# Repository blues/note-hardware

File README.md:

# note-hardware

This repository contains open hardware designs for Notecarriers and other Notecard-related hardware available through our [online store](https://shop.blues.com).

## Designs

|Item|Description|Contents|
|---|---|---|
|[Notecard](Notecard)|Device-to-cloud data pump|Dimensioned drawings and 3D models|
|[Notecarrier A](Notecarrier-A)|Carrier for battery- and solar-powered wireless applications|Full electrical and mechanical design, plus KiCad|
|[Notecarrier CX](Notecarrier-CX)|Carrier with an onboard STM32L433 MCU|Full electrical and mechanical design, plus KiCad|
|[Notecarrier F](Notecarrier-F)|Carrier for Adafruit Feather-compatible hosts|Full electrical and mechanical design, plus KiCad|
|[Notecarrier Pi](Notecarrier-Pi)|Carrier with a Raspberry Pi-compatible hardware interface|Full electrical and mechanical design, plus KiCad|
|[Notecarrier X](Notecarrier-X)|Small form-factor carrier with Qwiic and ESLOV ports|Full electrical and mechanical design, plus KiCad|
|[Notecarrier XI](Notecarrier-XI)|Companion carrier for Starnote for Iridium|Full electrical and mechanical design, plus KiCad|
|[Notecarrier XM](Notecarrier-XM)|Minimal small form-factor carrier, without an external SIM slot|Full electrical and mechanical design, plus KiCad|
|[Notecarrier XP](Notecarrier-XP)|Companion carrier for the Notecard XP|Full electrical and mechanical design|
|[Notecarrier XS](Notecarrier-XS)|Ultra-compact small form-factor carrier|Full electrical and mechanical design, plus KiCad|
|[Cygnet](Cygnet)|STM32L433 in Adafruit Feather form factor|Full electrical design, plus KiCad|
|[Swan](Swan)|STM32L4R5 in Adafruit Feather form factor|Full electrical and mechanical design|
|[Starnote](Starnote)|Satellite Notecard companion|3D models|
|[Scoop](Scoop)|Supercapacitor backup power for Notecard applications|Full electrical and mechanical design, plus KiCad|
|[Mojo](Mojo)|Energy-usage measurement for battery-powered systems|Full electrical and mechanical design, plus KiCad|
|[Airnote](Airnote)|Air quality monitor powered by Notecard|Enclosure 3D models and drawings|
|[Wireless for OPTA](Wireless%20for%20OPTA)|Cellular and Wi-Fi connectivity for Arduino Opta|3D model|
|[3D Models for Enclosures](3D%20Models%20for%20Enclosures)|Community-contributed enclosures, not supported by Blues|Printable STL and STEP models|
|[_Legacy Hardware](_Legacy%20Hardware)|Components and designs no longer sold|Assorted design files|

Each directory has its own README describing the available versions, the design
file formats, and any caveats that apply to that board.

## More Information

Various other resources that may be useful as you develop hardware around Notecard and Notecarriers.

### Application Notes

* [Antenna Guide](https://dev.blues.io/datasheets/application-notes/antenna-guide/)
* [Blues Security, Reliability, and Governance](https://dev.blues.io/datasheets/application-notes/blues-security-reliability-and-governance/)
* [Designing for XP Variants of the Blues Notecard](https://dev.blues.io/datasheets/application-notes/designing-for-xp-variants-of-the-blues-notecard/)
* [Low-Power Hardware Design](https://dev.blues.io/datasheets/application-notes/low-power-hardware-design/)
* [Notecard Carrier Board Design Guide](https://dev.blues.io/datasheets/application-notes/notecard-carrier-board-design-guide/)
* [Notecard Real-Time Clock](https://dev.blues.io/datasheets/application-notes/notecard-real-time-clock/)
* [Notecarrier A Series Solar JST Input](https://dev.blues.io/datasheets/application-notes/notecarrier-a-series-solar-jst-input/)
* [Starnote Carrier Board Design Guide](https://dev.blues.io/datasheets/application-notes/starnote-carrier-board-design-guide/)

### Tooling

The [_Tools](_Tools) directory holds the utilities used to maintain this
repository, including the KiCad validation harness that checks the KiCad ports
against the shipped fabrication packages.

### Learn more about Blues, Notecard, and Notehub

* [blues.com](https://blues.com)
* [notehub.io](https://notehub.io)
* [dev.blues.io](https://dev.blues.io)

## Contributing

We love issues, fixes, and pull requests from everyone. By participating in this
project, you agree to abide by the Blues Inc.
[code of conduct](CODE_OF_CONDUCT.md).

For details on contributions we accept and the process for contributing, see our
[contribution guide](CONTRIBUTING.md).

## License

Copyright (c) 2026 Blues Inc. Released under the MIT license. See
[LICENSE](LICENSE) for details.

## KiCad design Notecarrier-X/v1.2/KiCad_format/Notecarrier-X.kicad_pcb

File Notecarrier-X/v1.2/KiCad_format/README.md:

# Notecarrier-X — KiCad format

This directory contains the design files for the Blues **Notecarrier-X**
in **KiCad 9** format, ported from the internal Altium Designer sources
(project `100379_notecarrier-x`, Byte Lab Grupa d.o.o. for Blues) and
validated against the shipped production BOM and the published v1.2
fabrication package — see
[`documentation/Porting-Notes.md`](documentation/Porting-Notes.md) and
[`validation/`](validation/).

Generated from the design house's **Rev-11 release snapshot** — the Altium
sources behind the published v1.2 fab package (`2200-918`). Copper, solder mask
and paste match that fab package to within raster resolution, and every pad's
net matches the released board. An earlier version of this port was built from a post-v1.2
development state and carried a source-fidelity disclaimer; it was
regenerated from Rev-11 in October 2026 and the disclaimer retired (see the
Porting-Notes history section).

## Contents

| Path | Description |
|---|---|
| `Notecarrier-X.kicad_pro` / `.kicad_prl` | KiCad project |
| `Notecarrier-X.kicad_sch` | Root schematic sheet |
| `Notecarrier-X_IO-Connection.kicad_sch` | IO connection sheet |
| `Notecarrier-X_Notecard-Connection.kicad_sch` | Notecard connection sheet |
| `Notecarrier-X_Power.kicad_sch` | Power sheet |
| `Notecarrier-X.kicad_pcb` | 2-layer board (zone fills preserved from the Altium import — do not refill) |
| `Notecarrier-X.kicad_wks` | Drawing sheet (shared Blues template) |
| `Notecarrier-X-altium-import.kicad_sym` / `.pretty/` | Project libraries captured during the import |
| `sym-lib-table` / `fp-lib-table` | Library tables |
| `documentation/` | Porting notes (provenance and verification), plotted PDFs, and the board-regeneration scripts (`scripts/`, also used for Notecarrier-XM) |
| `manufacturing/Notecarrier-X_RevA.zip` | KiCad-exported gerbers + drill |
| `validation/` | Validation-gate artifacts (ERC/DRC/BOM reports, per-layer gerber diffs, kicanvas renders) |

The schematic references the shared Blues symbol/footprint library via the
`BLUES_KICAD_LIB_DIR` path variable
([blues-kicad-lib](https://github.com/blues/blues-kicad-lib)), with all
symbols and footprints used by this design also embedded in the project
libraries above, so the project opens standalone.

## Provenance

Ported from Altium Designer sources with KiCad 9.0.9's importer and the
validation harness in
[`_Tools/kicad_validation/`](../../../_Tools/kicad_validation/). The original
Altium sources are internal and are not part of this repository; the
published v1.2 fabrication package (`../2200-918__2024-06-06.zip`), BOM
(`../BOM-3000-794-001.xlsx`) and drawings in the parent folder remain the
manufacturing ground truth for the shipped product.

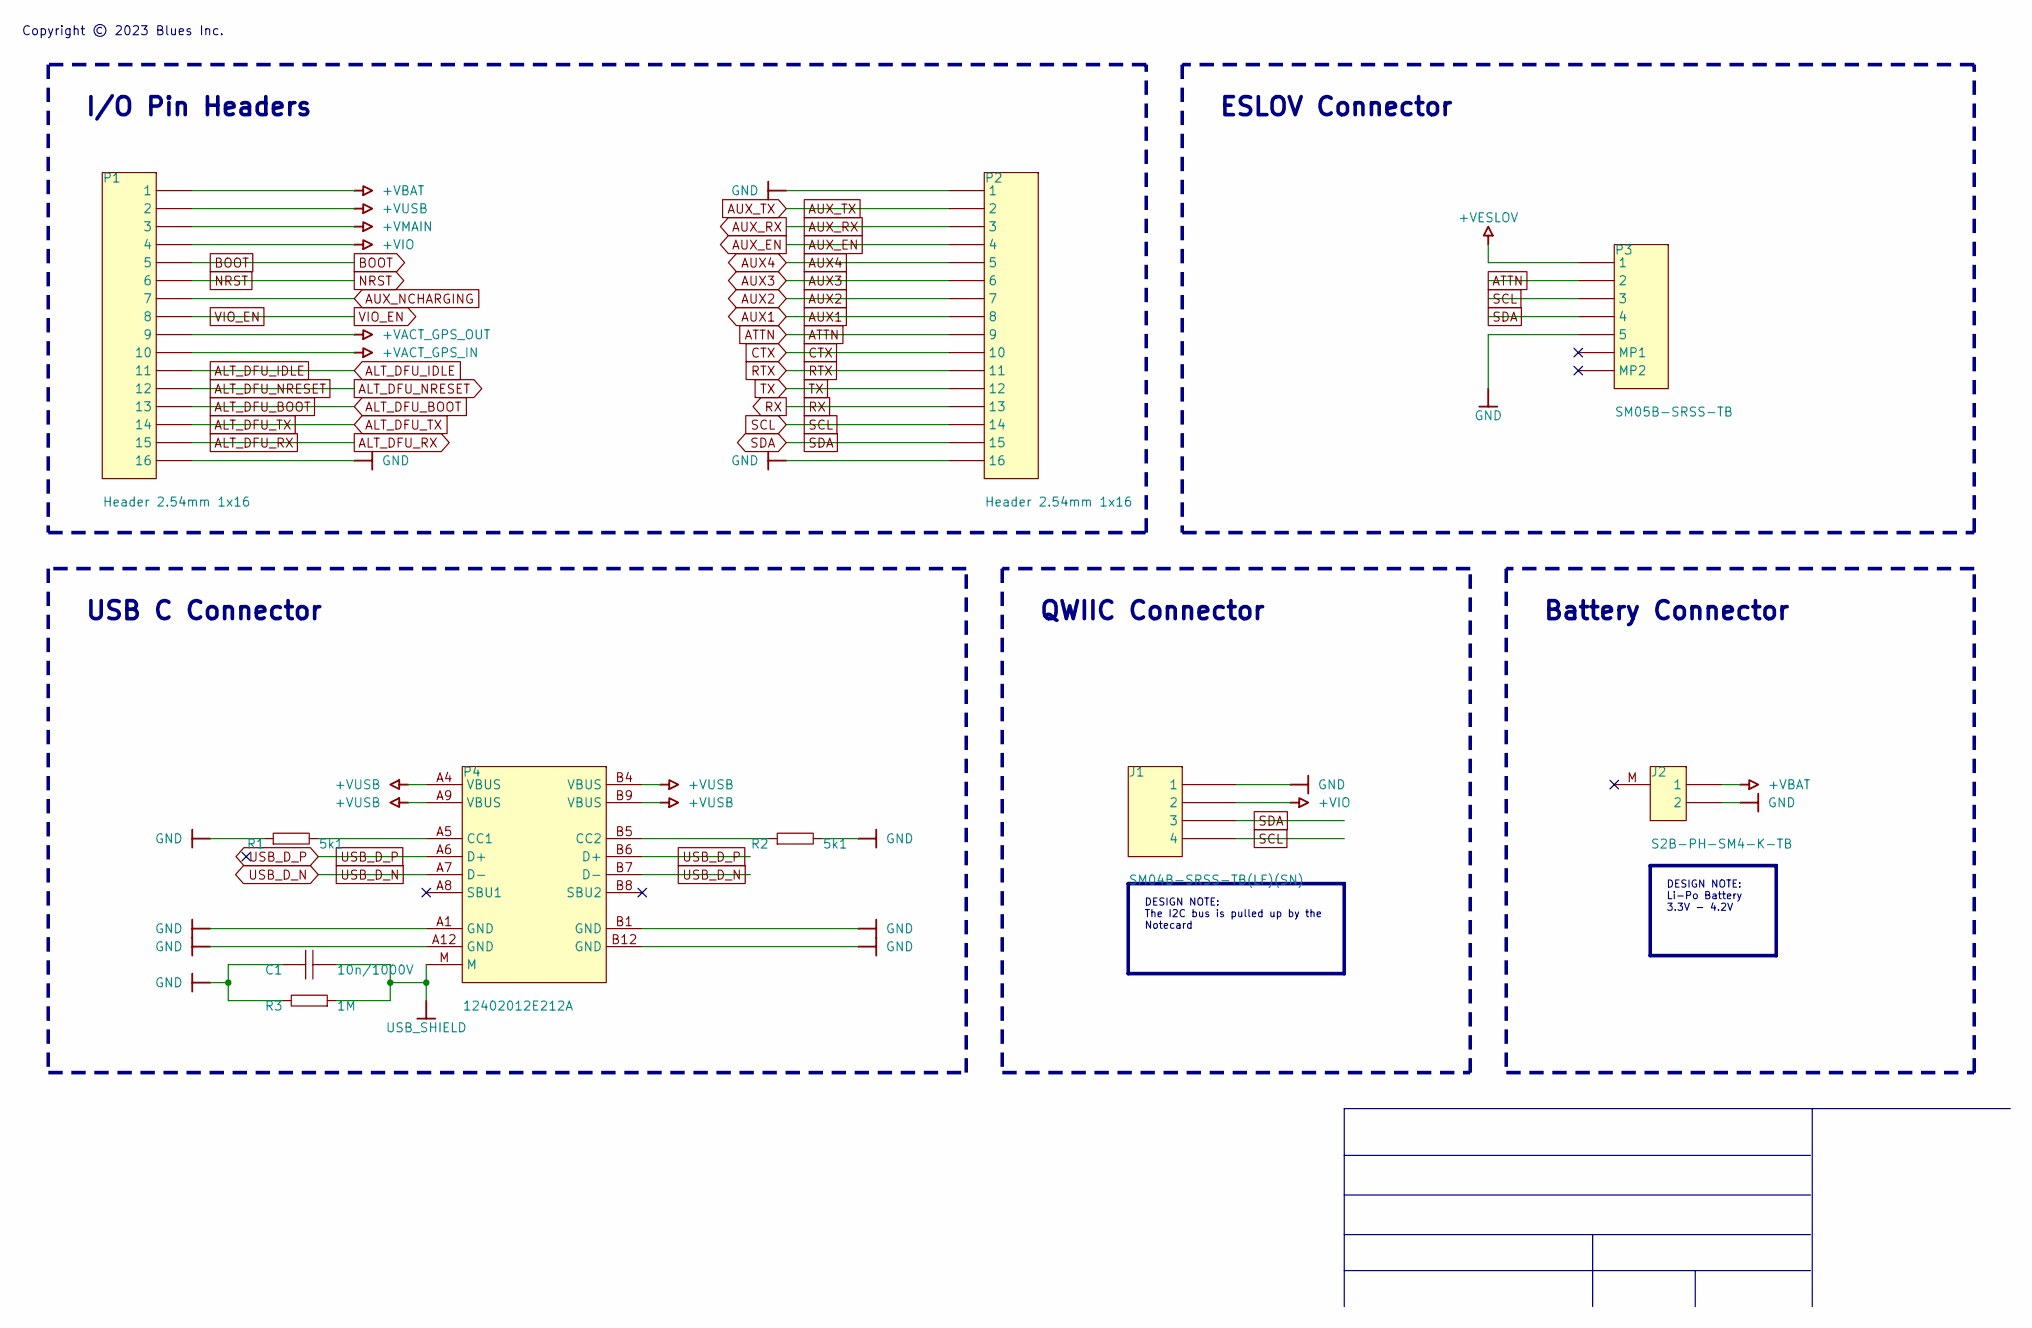
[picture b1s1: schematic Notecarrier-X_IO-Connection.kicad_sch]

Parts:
C1: 10n/1000V; C-1206; MANUFACTURER PART NUMBER CS1206KKX7RCBB103
J1: SM04B-SRSS-TB(LF)(SN); JST SM04B-SRSS-TB; MANUFACTURER PART NUMBER SM04B-SRSS-TB(LF)(SN)
J2: S2B-PH-SM4-K-TB; Conn S2B-PH-SM4; MANUFACTURER PART NUMBER S2B-PH-SM4-K-TB(LF)(SN)
P1, P2: Header 2.54mm 1x16; Header 2.54mm 1X16; MANUFACTURER PART NUMBER N/A
P3: SM05B-SRSS-TB; Conn_SM05B-SRSS-TB; MANUFACTURER PART NUMBER SM05B-SRSS-TB
P4: 12402012E212A; CONN_12402012E212A; MANUFACTURER PART NUMBER 12402012E212A
R1, R2: 5k1; R-0402; MANUFACTURER PART NUMBER N/A
R3: 1M; R-1206; MANUFACTURER PART NUMBER N/A

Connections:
+VACT_GPS_IN: P1.10; also elsewhere on the board
+VACT_GPS_OUT: P1.9; also elsewhere on the board
+VBAT: J2.1, P1.1; also elsewhere on the board
+VESLOV: P3.1; also elsewhere on the board
+VIO: J1.2, P1.4; also elsewhere on the board
+VMAIN: P1.3; also elsewhere on the board
+VUSB: P1.2, P4.A4 (VBUS), P4.A9 (VBUS), P4.B4 (VBUS), P4.B9 (VBUS); also elsewhere on the board
ALT_DFU_BOOT: P1.13; also elsewhere on the board
ALT_DFU_IDLE: P1.11; also elsewhere on the board
ALT_DFU_NRESET: P1.12; also elsewhere on the board
ALT_DFU_RX: P1.15; also elsewhere on the board
ALT_DFU_TX: P1.14; also elsewhere on the board
ATTN: P2.9, P3.2; also elsewhere on the board
AUX1: P2.8; also elsewhere on the board
AUX2: P2.7; also elsewhere on the board
AUX3: P2.6; also elsewhere on the board
AUX4: P2.5; also elsewhere on the board
AUX_EN: P2.4; also elsewhere on the board
AUX_NCHARGING: P1.7; also elsewhere on the board
AUX_RX: P2.3; also elsewhere on the board
AUX_TX: P2.2; also elsewhere on the board
BOOT: P1.5; also elsewhere on the board
CTX: P2.10; also elsewhere on the board
GND: C1.2, J1.1, J2.2, P1.16, P2.1, P2.16, P3.5, P4.A1 (GND), P4.A12 (GND), P4.B1 (GND), P4.B12 (GND), R1.1, R2.2, R3.2; also elsewhere on the board
NRST: P1.6; also elsewhere on the board
unnamed: P4.A5 (CC1), R1.2
unnamed: P4.B5 (CC2), R2.1
RTX: P2.11; also elsewhere on the board
RX: P2.13; also elsewhere on the board
SCL: J1.4, P2.14, P3.3; also elsewhere on the board
SDA: J1.3, P2.15, P3.4; also elsewhere on the board
TX: P2.12; also elsewhere on the board
USB_D_N: P4.A7 (D-), P4.B7 (D-); also elsewhere on the board
USB_D_P: P4.A6 (D+), P4.B6 (D+); also elsewhere on the board
USB_SHIELD: C1.1, P4.M, R3.1
VIO_EN: P1.8; also elsewhere on the board

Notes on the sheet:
ESLOV Connector
Battery Connector
USB C Connector
QWIIC Connector
I/O Pin Headers
Copyright © 2023 Blues Inc.
DESIGN NOTE: Li-Po Battery 3.3V - 4.2V
DESIGN NOTE: The I2C bus is pulled up by the Notecard

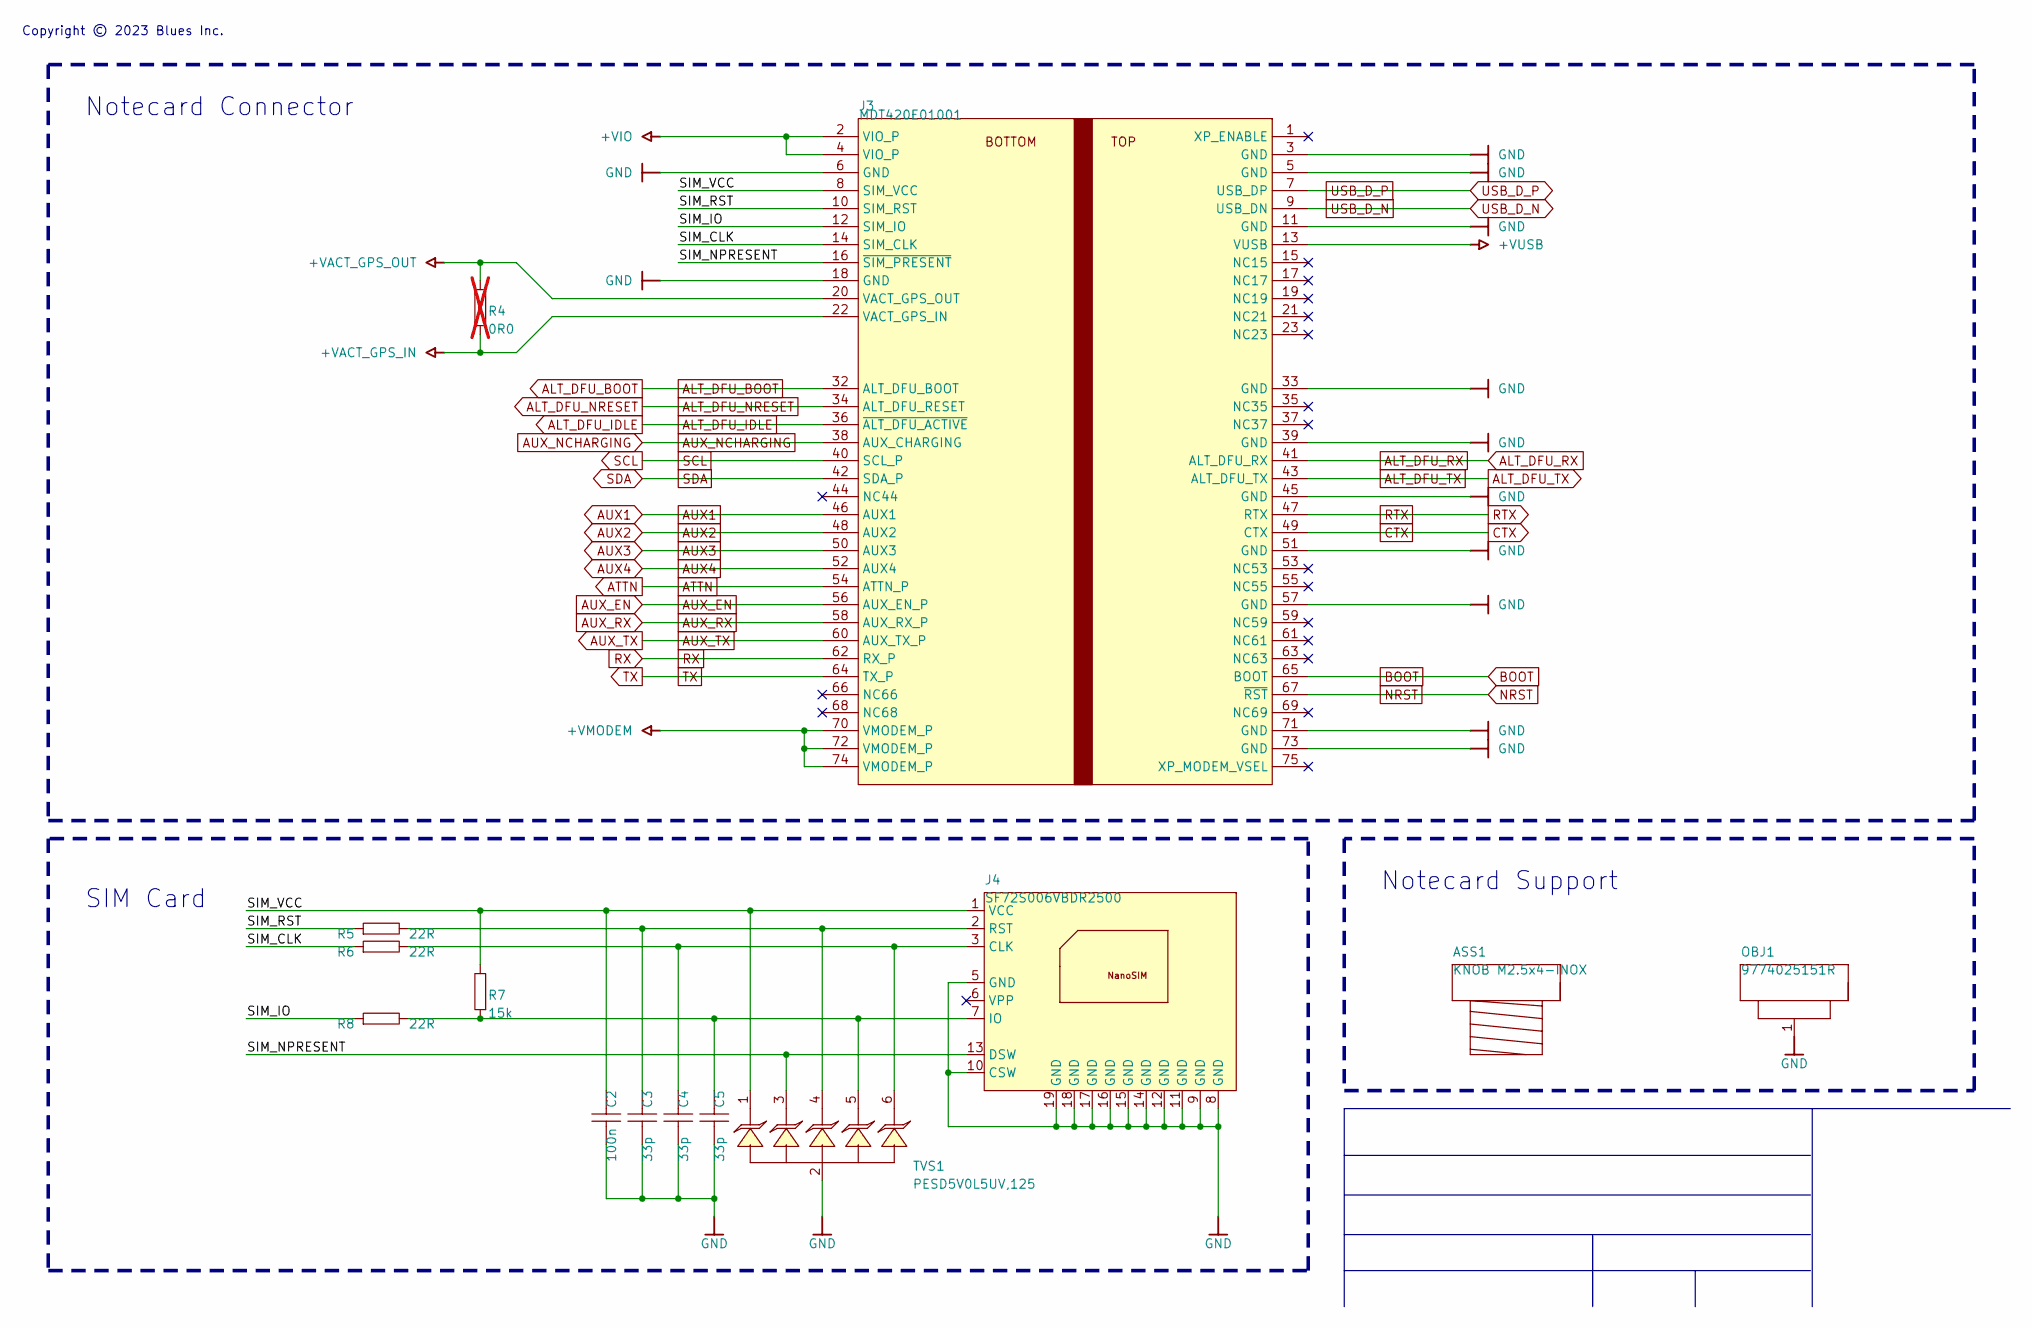
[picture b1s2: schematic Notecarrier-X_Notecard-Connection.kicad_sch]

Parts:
ASS1: KNOB M2.5x4-INOX; MANUFACTURER PART NUMBER M2.5X4/D7985-A2
C2: 100n; C-0402; MANUFACTURER PART NUMBER N/A
C3, C4, C5: 33p; C-0402; MANUFACTURER PART NUMBER N/A
J3: MDT420E01001; J-75-0050-MOS-M2; MANUFACTURER PART NUMBER MDT420E03001
J4: SF72S006VBDR2500; J-NANOSIM-SF72S006VBA; MANUFACTURER PART NUMBER SF72S006VBDR2500
OBJ1: 9774025151R; DIST-WASMSIM0250; MANUFACTURER PART NUMBER 9774025151R
R4: 0R0; R-0603; MANUFACTURER PART NUMBER N/A; not fitted
R5, R6, R8: 22R; R-0402; MANUFACTURER PART NUMBER N/A
R7: 15k; R-0402; MANUFACTURER PART NUMBER N/A
TVS1: PESD5V0L5UV,125; SOT666; MANUFACTURER PART NUMBER PESD5V0L5UV,125

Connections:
+VACT_GPS_IN: J3.22 (VACT_GPS_IN), R4.1; also elsewhere on the board
+VACT_GPS_OUT: J3.20 (VACT_GPS_OUT), R4.2; also elsewhere on the board
+VIO: J3.2 (VIO_P), J3.4 (VIO_P); also elsewhere on the board
+VMODEM: J3.70 (VMODEM_P), J3.72 (VMODEM_P), J3.74 (VMODEM_P); also elsewhere on the board
+VUSB: J3.13 (VUSB); also elsewhere on the board
/Notecard Connection/SIM_CLK: J3.14 (SIM_CLK), R6.1
/Notecard Connection/SIM_IO: J3.12 (SIM_IO), R8.1
/Notecard Connection/SIM_NPRESENT: J3.16 (~SIM_PRESENT), J4.13 (DSW), TVS1.3 (C3)
/Notecard Connection/SIM_RST: J3.10 (SIM_RST), R5.1
/Notecard Connection/SIM_VCC: C2.2, J3.8 (SIM_VCC), J4.1 (VCC), R7.2, TVS1.1 (C1)
ALT_DFU_BOOT: J3.32 (ALT_DFU_BOOT); also elsewhere on the board
ALT_DFU_IDLE: J3.36 (~ALT_DFU_ACTIVE); also elsewhere on the board
ALT_DFU_NRESET: J3.34 (ALT_DFU_RESET); also elsewhere on the board
ALT_DFU_RX: J3.41 (ALT_DFU_RX); also elsewhere on the board
ALT_DFU_TX: J3.43 (ALT_DFU_TX); also elsewhere on the board
ATTN: J3.54 (ATTN_P); also elsewhere on the board
AUX1: J3.46 (AUX1); also elsewhere on the board
AUX2: J3.48 (AUX2); also elsewhere on the board
AUX3: J3.50 (AUX3); also elsewhere on the board
AUX4: J3.52 (AUX4); also elsewhere on the board
AUX_EN: J3.56 (AUX_EN_P); also elsewhere on the board
AUX_NCHARGING: J3.38 (AUX_CHARGING); also elsewhere on the board
AUX_RX: J3.58 (AUX_RX_P); also elsewhere on the board
AUX_TX: J3.60 (AUX_TX_P); also elsewhere on the board
BOOT: J3.65 (BOOT); also elsewhere on the board
CTX: J3.49 (CTX); also elsewhere on the board
GND: C2.1, C3.1, C4.1, C5.1, J3.3 (GND), J3.5 (GND), J3.6 (GND), J3.11 (GND), J3.18 (GND), J3.33 (GND), J3.39 (GND), J3.45 (GND), J3.51 (GND), J3.57 (GND), J3.71 (GND), J3.73 (GND), J4.5 (GND), J4.8 (GND), J4.9 (GND), J4.10 (CSW), J4.11 (GND), J4.12 (GND), J4.14 (GND), J4.15 (GND), J4.16 (GND), J4.17 (GND), J4.18 (GND), J4.19 (GND), OBJ1.1, TVS1.2 (A2); also elsewhere on the board
NRST: J3.67 (~RST); also elsewhere on the board
unnamed: C4.2, J4.3 (CLK), R6.2, TVS1.6 (C6)
unnamed: C5.2, J4.7 (IO), R7.1, R8.2, TVS1.5 (A5)
unnamed: C3.2, J4.2 (RST), R5.2, TVS1.4 (C4)
RTX: J3.47 (RTX); also elsewhere on the board
RX: J3.62 (RX_P); also elsewhere on the board
SCL: J3.40 (SCL_P); also elsewhere on the board
SDA: J3.42 (SDA_P); also elsewhere on the board
TX: J3.64 (TX_P); also elsewhere on the board
USB_D_N: J3.9 (USB_DN); also elsewhere on the board
USB_D_P: J3.7 (USB_DP); also elsewhere on the board

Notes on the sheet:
Notecard Support
Copyright © 2023 Blues Inc.
Notecard Connector
SIM Card

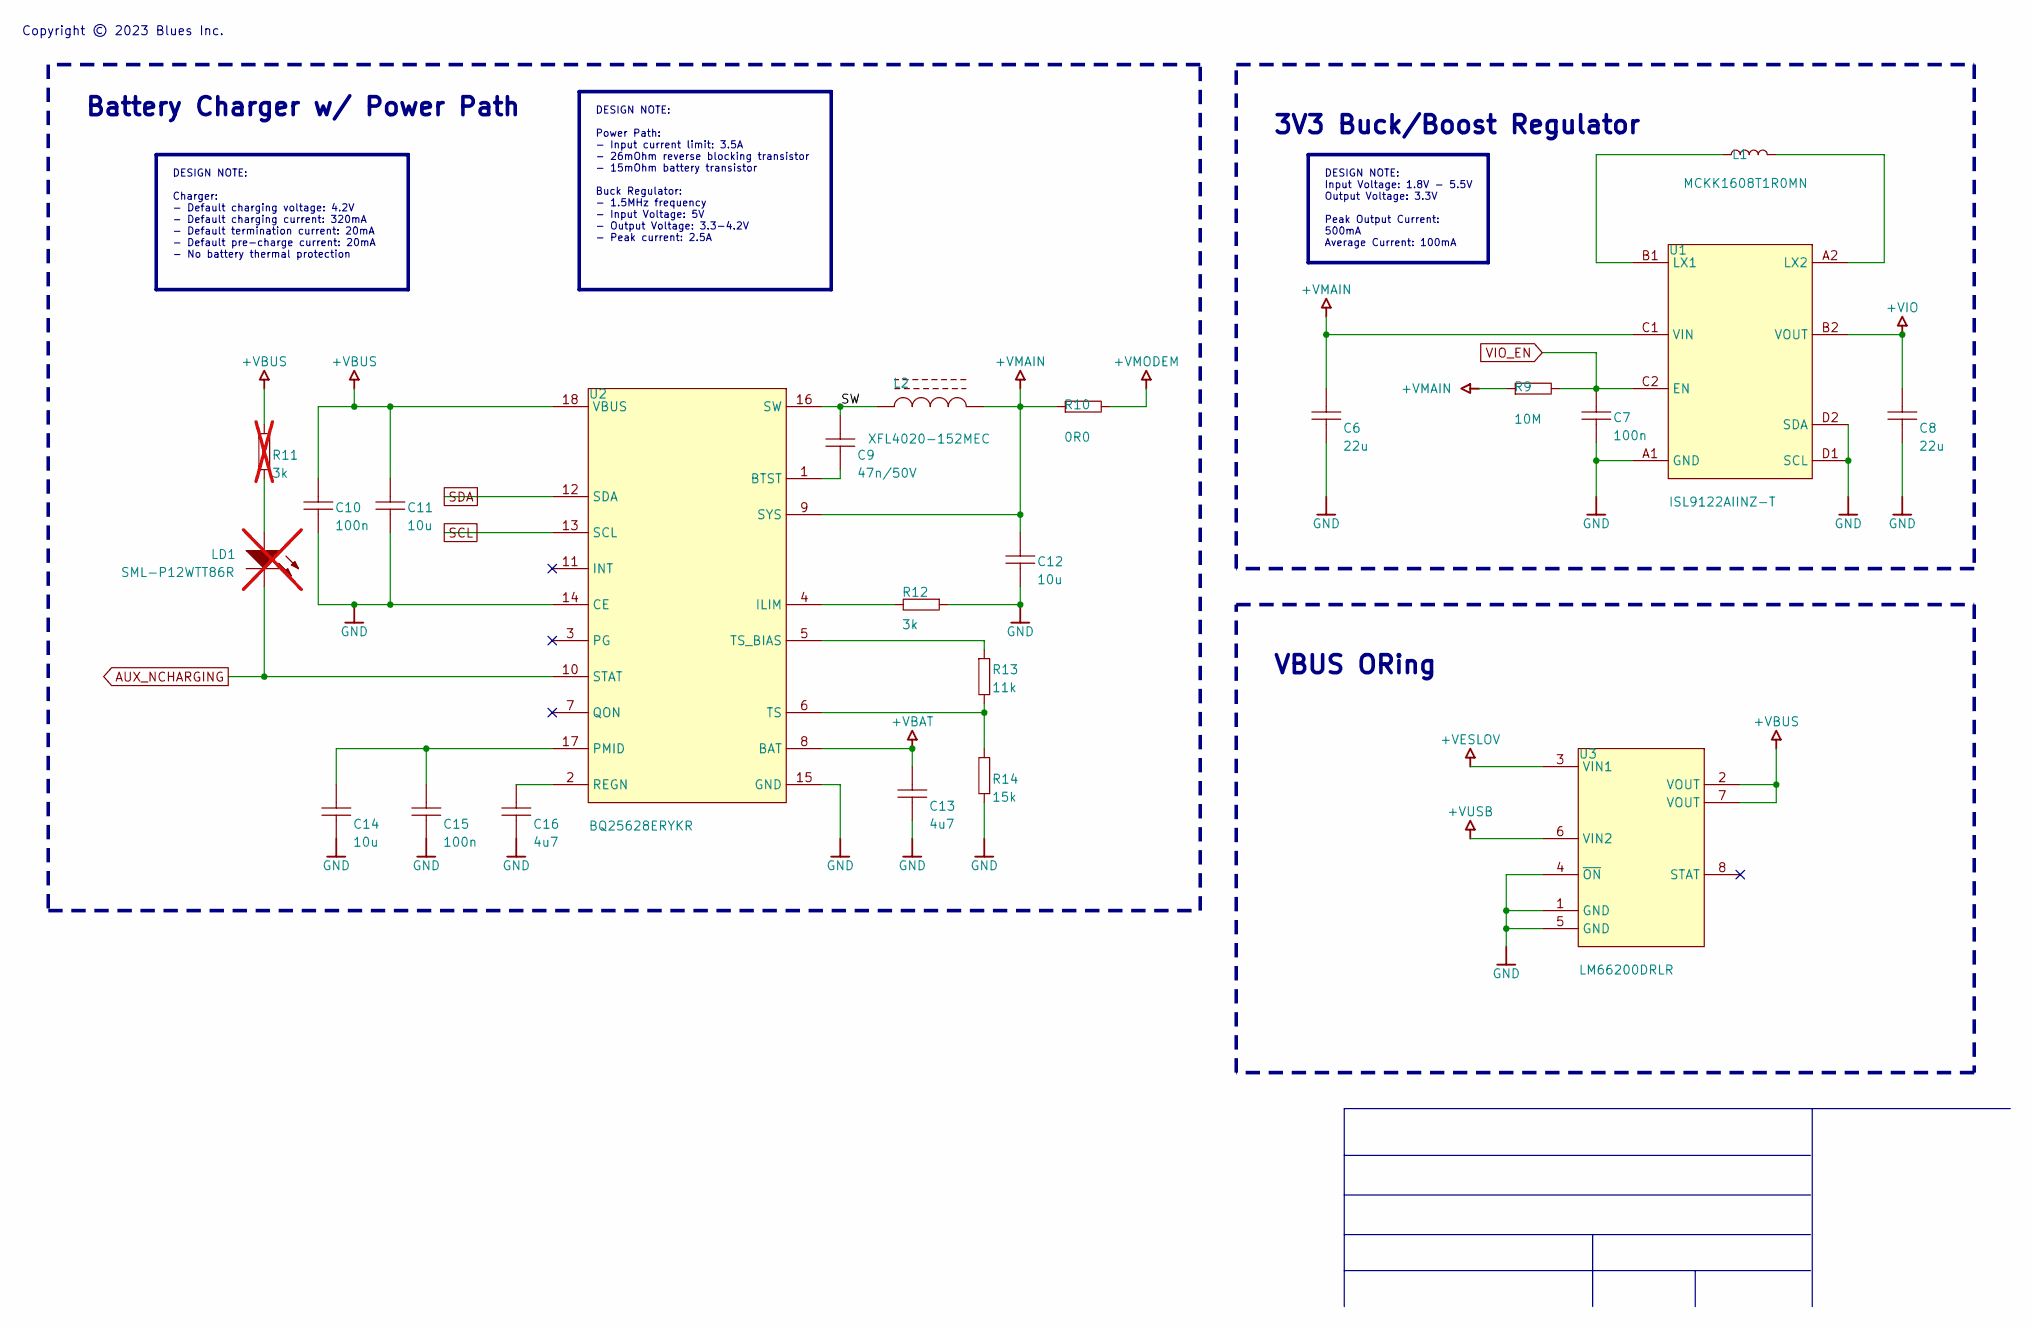
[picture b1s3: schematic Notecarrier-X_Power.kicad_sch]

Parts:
C6, C8: 22u; C-0805; MANUFACTURER PART NUMBER N/A
C7, C10, C15: 100n; C-0402; MANUFACTURER PART NUMBER N/A
C9: 47n/50V; C-0402; MANUFACTURER PART NUMBER N/A
C11, C12: 10u; C-1206; MANUFACTURER PART NUMBER N/A
C13, C16: 4u7; C-0603; MANUFACTURER PART NUMBER N/A
C14: 10u; C-0805; MANUFACTURER PART NUMBER GRM21BR61E106MA73L
L1: MCKK1608T1R0MN; L-0603; MANUFACTURER PART NUMBER MCKK1608T1R0MN
L2: XFL4020-152MEC; IND_XFL4020; MANUFACTURER PART NUMBER XFL4020-152MEC
LD1: SML-P12WTT86R; LED-0402; MANUFACTURER PART NUMBER SML-P12WTT86R; not fitted
R9: 10M; R-0402; MANUFACTURER PART NUMBER N/A
R10: 0R0; R-0603; MANUFACTURER PART NUMBER N/A
R11: 3k; R-0402; MANUFACTURER PART NUMBER N/A; not fitted
R12: 3k; R-0402; MANUFACTURER PART NUMBER N/A
R13: 11k; R-0402; MANUFACTURER PART NUMBER N/A
R14: 15k; R-0402; MANUFACTURER PART NUMBER N/A
U1: ISL9122AIINZ-T; BGA8N40P2X4_180x100x50; MANUFACTURER PART NUMBER ISL9122AIINZ-T
U2: BQ25628ERYKR; QFN40P300X150X80-18N; MANUFACTURER PART NUMBER BQ25628ERYKR
U3: LM66200DRLR; SOT-583; MANUFACTURER PART NUMBER LM66200DRLR

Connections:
+VBAT: C13.2, U2.8 (BAT); also elsewhere on the board
+VBUS: C10.1, C11.1, R11.2, U2.18 (VBUS), U3.2 (VOUT), U3.7 (VOUT)
+VESLOV: U3.3 (VIN1); also elsewhere on the board
+VIO: C8.2, U1.B2 (VOUT); also elsewhere on the board
+VMAIN: C6.2, C12.1, L2.2, R9.1, R10.1, U1.C1 (VIN), U2.9 (SYS); also elsewhere on the board
+VMODEM: R10.2; also elsewhere on the board
+VUSB: U3.6 (VIN2); also elsewhere on the board
/Power/SW: C9.2, L2.1, U2.16 (SW)
AUX_NCHARGING: LD1.2 (K), U2.10 (STAT); also elsewhere on the board
GND: C6.1, C7.2, C8.1, C10.2, C11.2, C12.2, C13.1, C14.1, C15.1, C16.1, R12.1, R14.1, U1.A1 (GND), U1.D1 (SCL), U1.D2 (SDA), U2.14 (CE), U2.15 (GND), U3.1 (GND), U3.4 (~ON), U3.5 (GND); also elsewhere on the board
unnamed: LD1.1 (A), R11.1
unnamed: L1.1, U1.B1 (LX1)
unnamed: L1.2, U1.A2 (LX2)
unnamed: C9.1, U2.1 (BTST)
unnamed: R12.2, U2.4 (ILIM)
unnamed: C14.2, C15.2, U2.17 (PMID)
unnamed: C16.2, U2.2 (REGN)
unnamed: R13.2, R14.2, U2.6 (TS)
unnamed: R13.1, U2.5 (TS_BIAS)
SCL: U2.13 (SCL); also elsewhere on the board
SDA: U2.12 (SDA); also elsewhere on the board
VIO_EN: C7.1, R9.2, U1.C2 (EN); also elsewhere on the board

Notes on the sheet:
Copyright © 2023 Blues Inc.
Battery Charger w/ Power Path
VBUS ORing
3V3 Buck/Boost Regulator
DESIGN NOTE: Charger: - Default charging voltage: 4.2V - Default charging current: 320mA - Default termination current: 20mA - Default pre-charge current: 20mA - No battery thermal protection
DESIGN NOTE: Power Path: - Input current limit: 3.5A - 26mOhm reverse blocking transistor - 15mOhm battery transistor Buck Regulator: - 1.5MHz frequency - Input Voltage: 5V - Output Voltage: 3.3-4.2V - Peak current: 2.5A
DESIGN NOTE: Input Voltage: 1.8V - 5.5V Output Voltage: 3.3V Peak Output Current: 500mA Average Current: 100mA

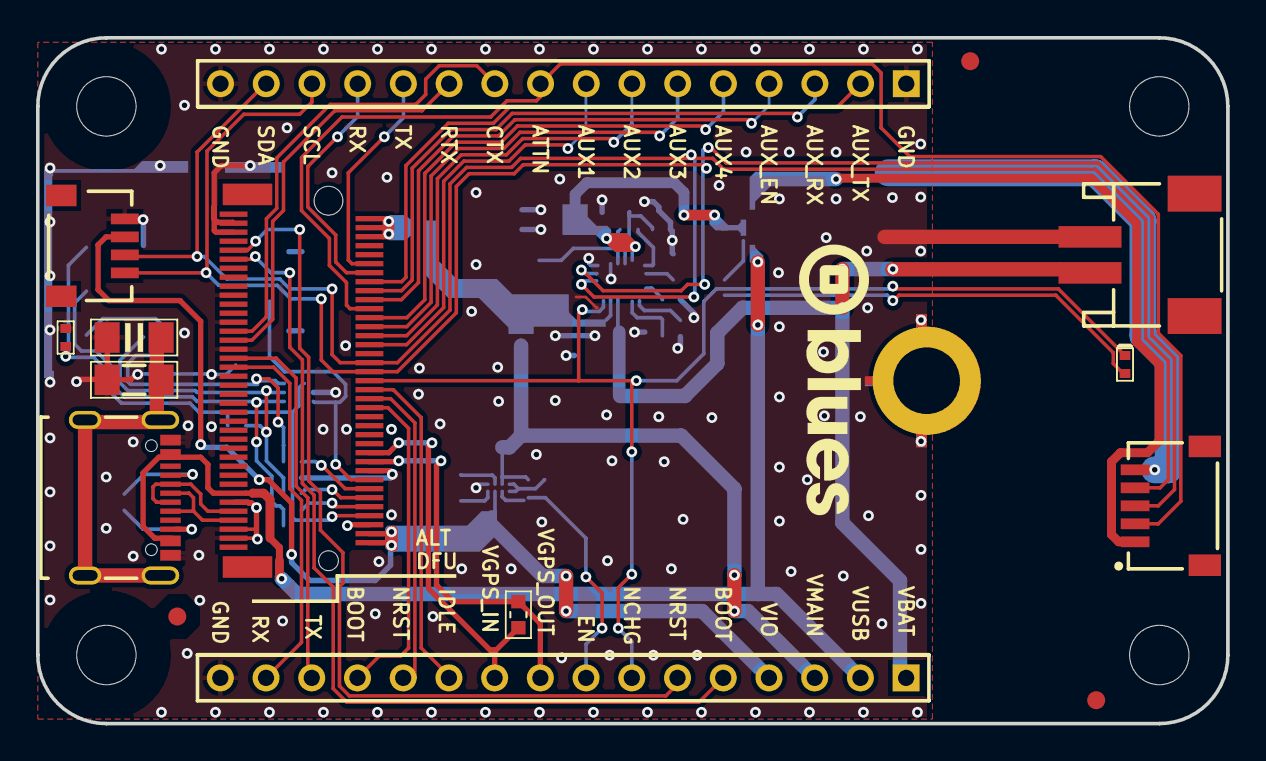
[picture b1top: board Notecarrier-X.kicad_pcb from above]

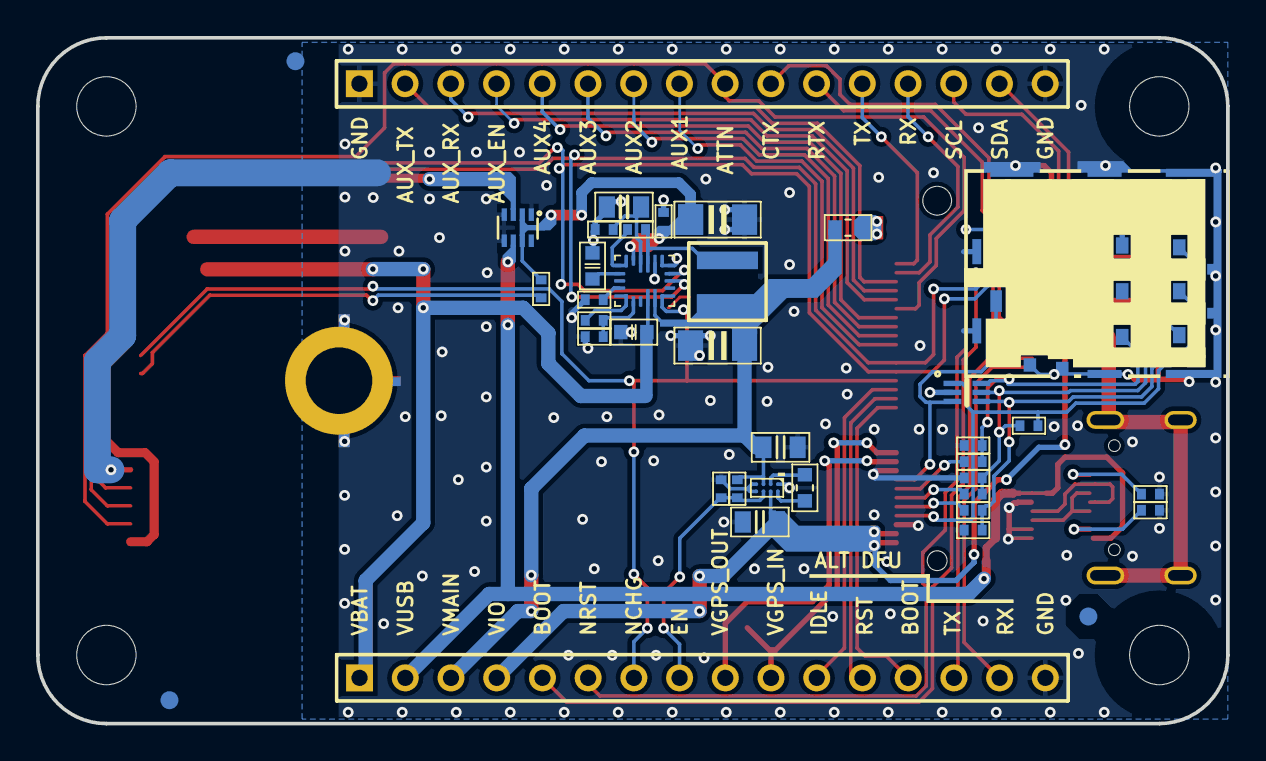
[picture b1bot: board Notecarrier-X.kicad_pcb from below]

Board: 2 copper layers, 66.1 x 38.1 mm, 52 parts (36 on the bottom side), 56 nets.

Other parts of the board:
FD1, FD2, FD3, FD4, FD5, FD6: Fiducial mark; Fiducial mark 1mm

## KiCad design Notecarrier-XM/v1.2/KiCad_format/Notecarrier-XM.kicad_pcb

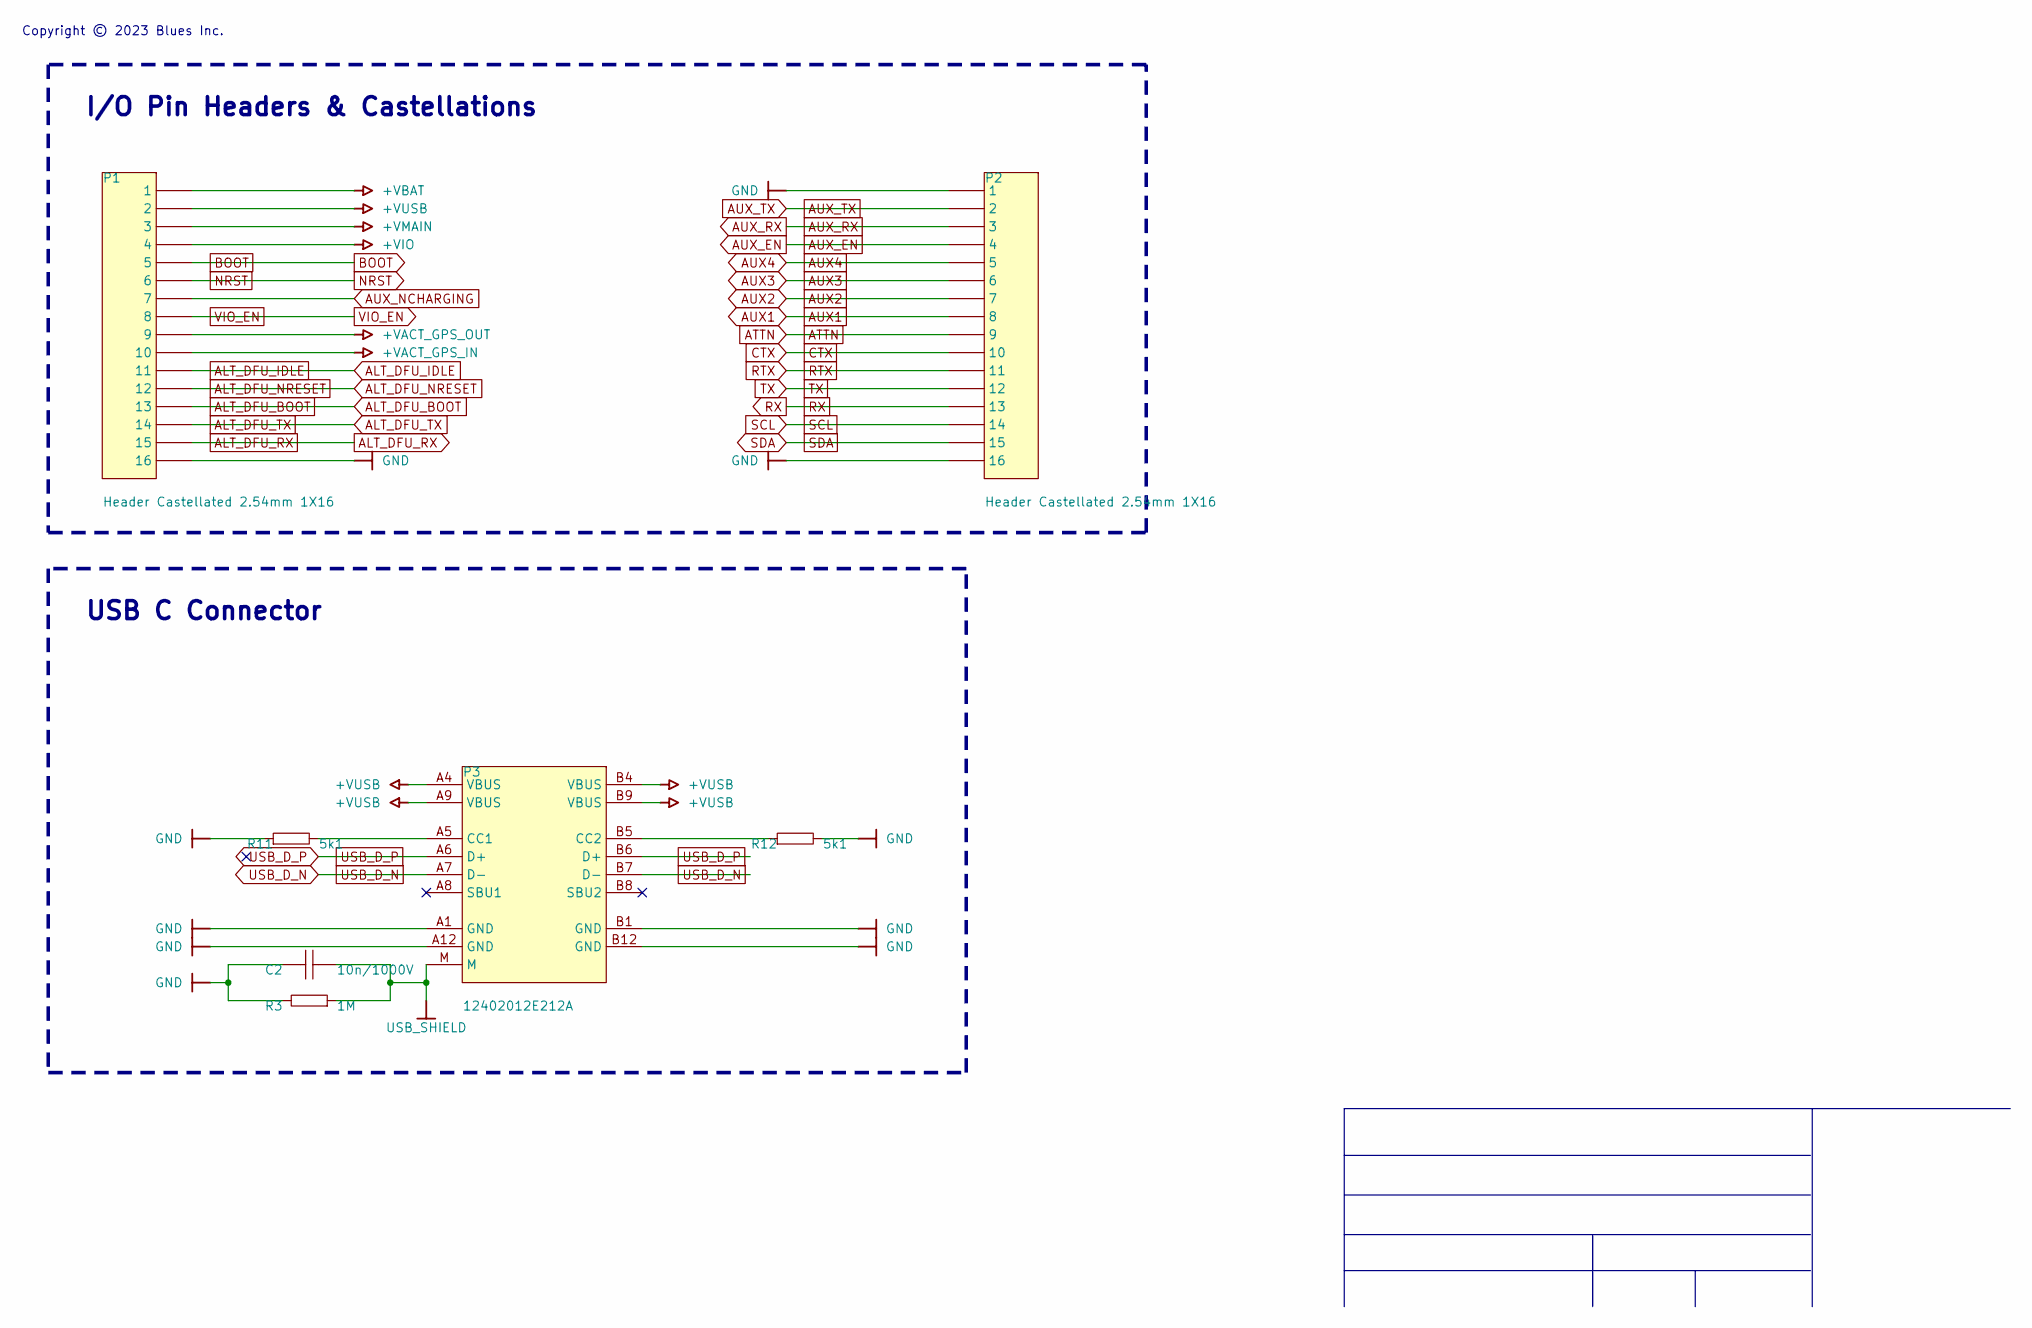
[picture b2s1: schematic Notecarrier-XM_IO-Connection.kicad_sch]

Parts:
C2: 10n/1000V; C-1206; MANUFACTURER PART NUMBER CS1206KKX7RCBB103
P1, P2: Header Castellated 2.54mm 1X16; Castellated Header 2.54mm 1X16; MANUFACTURER PART NUMBER N/A
P3: 12402012E212A; CONN_12402012E212A; MANUFACTURER PART NUMBER 12402012E212A
R3: 1M; R-1206; MANUFACTURER PART NUMBER N/A
R11, R12: 5k1; R-0402; MANUFACTURER PART NUMBER N/A

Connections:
+VACT_GPS_IN: P1.10; also elsewhere on the board
+VACT_GPS_OUT: P1.9; also elsewhere on the board
+VBAT: P1.1; also elsewhere on the board
+VIO: P1.4; also elsewhere on the board
+VMAIN: P1.3; also elsewhere on the board
+VUSB: P1.2, P3.A4 (VBUS), P3.A9 (VBUS), P3.B4 (VBUS), P3.B9 (VBUS); also elsewhere on the board
ALT_DFU_BOOT: P1.13; also elsewhere on the board
ALT_DFU_IDLE: P1.11; also elsewhere on the board
ALT_DFU_NRESET: P1.12; also elsewhere on the board
ALT_DFU_RX: P1.15; also elsewhere on the board
ALT_DFU_TX: P1.14; also elsewhere on the board
ATTN: P2.9; also elsewhere on the board
AUX1: P2.8; also elsewhere on the board
AUX2: P2.7; also elsewhere on the board
AUX3: P2.6; also elsewhere on the board
AUX4: P2.5; also elsewhere on the board
AUX_EN: P2.4; also elsewhere on the board
AUX_NCHARGING: P1.7; also elsewhere on the board
AUX_RX: P2.3; also elsewhere on the board
AUX_TX: P2.2; also elsewhere on the board
BOOT: P1.5; also elsewhere on the board
CTX: P2.10; also elsewhere on the board
GND: C2.2, P1.16, P2.1, P2.16, P3.A1 (GND), P3.A12 (GND), P3.B1 (GND), P3.B12 (GND), R3.2, R11.1, R12.2; also elsewhere on the board
NRST: P1.6; also elsewhere on the board
unnamed: P3.A5 (CC1), R11.2
unnamed: P3.B5 (CC2), R12.1
RTX: P2.11; also elsewhere on the board
RX: P2.13; also elsewhere on the board
SCL: P2.14; also elsewhere on the board
SDA: P2.15; also elsewhere on the board
TX: P2.12; also elsewhere on the board
USB_D_N: P3.A7 (D-), P3.B7 (D-); also elsewhere on the board
USB_D_P: P3.A6 (D+), P3.B6 (D+); also elsewhere on the board
USB_SHIELD: C2.1, P3.M, R3.1
VIO_EN: P1.8; also elsewhere on the board

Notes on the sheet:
I/O Pin Headers & Castellations
USB C Connector
Copyright © 2023 Blues Inc.

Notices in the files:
Notecarrier-A/v2.0/KiCad_format/Notecarrier-A.kicad_pcb:
Blues Inc (Copyright (c) 2023 Blues Inc)
